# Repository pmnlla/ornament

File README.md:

# ornament
weird ahh christmas ornament shaped pcb with neopixels, stm8, and battery charging support. todo add an ftdi ig?

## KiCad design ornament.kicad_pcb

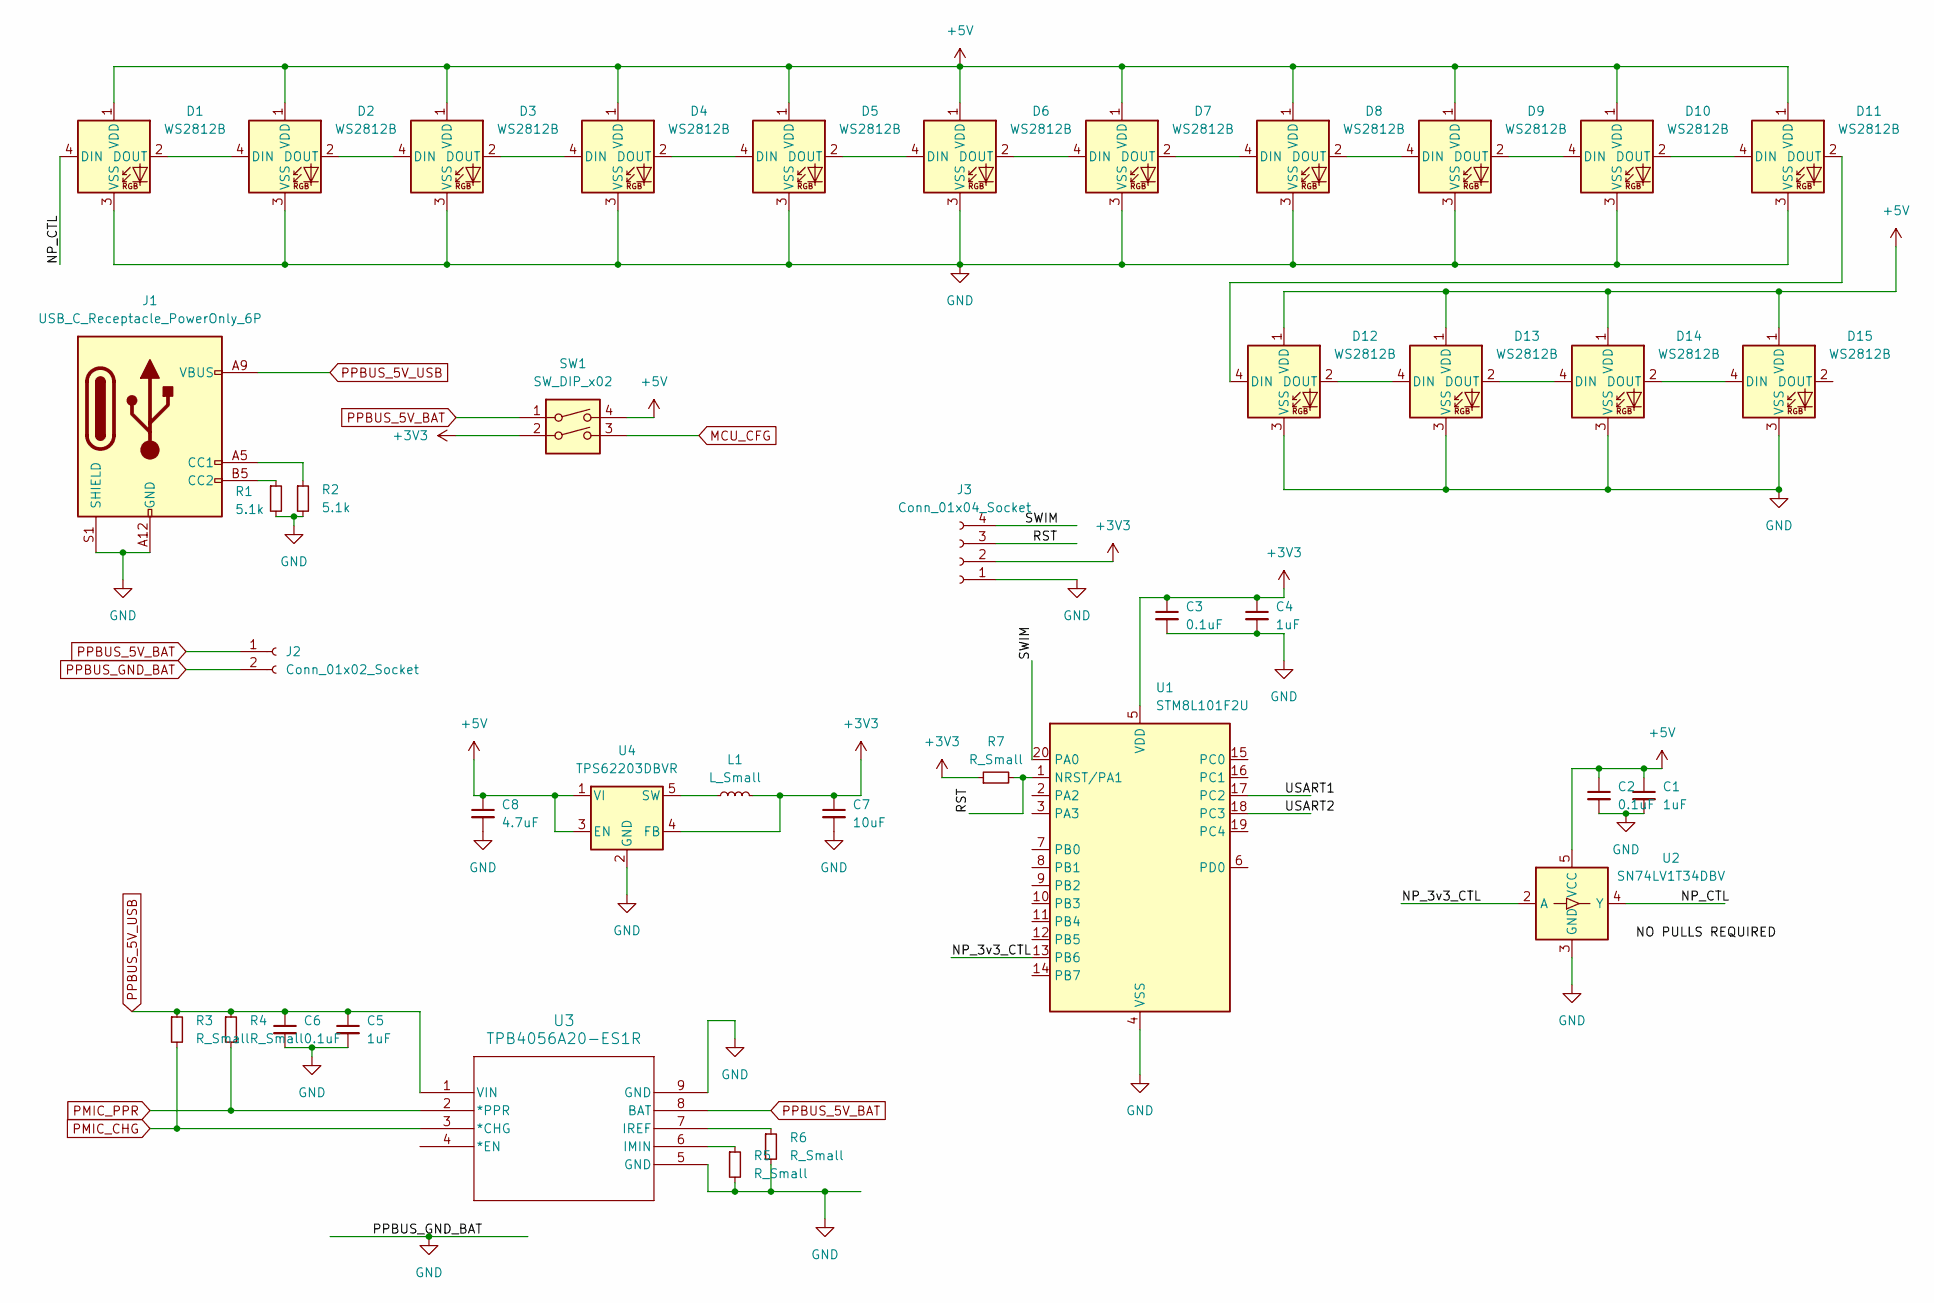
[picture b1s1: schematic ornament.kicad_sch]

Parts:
C1, C4, C5: 1uF; C_1206_3216Metric
C2, C3, C6: 0.1uF; C_1206_3216Metric
C7: 10uF; C_1206_3216Metric
C8: 4.7uF; C_1206_3216Metric
D1, D2, D3, D4, D5, D6, D7, D8, D9, D10, D11, D12, D13, D14, D15: WS2812B; LED_WS2812B_PLCC4_5.0x5.0mm_P3.2mm
J1: USB_C_Receptacle_PowerOnly_6P; USB_C_Receptacle_GCT_USB4125-xx-x-0190_6P_TopMnt_Horizontal
J2: Conn_01x02_Socket; JST_JWPF_B02B-JWPF-SK-R_1x02_P2.00mm_Vertical
J3: Conn_01x04_Socket; JST_ZE_S04B-ZESK-2D_1x04_P1.50mm_Horizontal
L1: L_Small; L_1206_3216Metric
R1, R2: 5.1k; R_1206_3216Metric
R3, R4, R5, R6, R7: R_Small; R_1206_3216Metric
SW1: SW_DIP_x02; SW_DIP_SPSTx02_Slide_6.7x6.64mm_W6.73mm_P2.54mm_LowProfile_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
U1: STM8L101F2U; ST_UFQFPN-20_3x3mm_P0.5mm
U2: SN74LV1T34DBV; SOT-23-5
U3: TPB4056A20-ES1R; ESOP-8_TPK
U4: TPS62203DBVR; SOT-23-5

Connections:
+3V3: C3.1, C4.1, C7.1, J3.2, L1.2, R7.1, SW1.2, U1.5 (VDD), U4.4 (FB)
+5V: C1.1, C2.1, C8.1, D1.1 (VDD), D2.1 (VDD), D3.1 (VDD), D4.1 (VDD), D5.1 (VDD), D6.1 (VDD), D7.1 (VDD), D8.1 (VDD), D9.1 (VDD), D10.1 (VDD), D11.1 (VDD), D12.1 (VDD), D13.1 (VDD), D14.1 (VDD), D15.1 (VDD), SW1.4, U2.5 (VCC), U4.1 (VI), U4.3 (EN)
/NP_3v3_CTL: U1.13 (PB6), U2.2 (A)
/NP_CTL: D1.4 (DIN), U2.4 (Y)
/RST: J3.3, R7.2, U1.1 (NRST/PA1)
/SWIM: J3.4, U1.20 (PA0)
/USART1: U1.17 (PC2)
/USART2: U1.18 (PC3)
MCU_CFG: SW1.3
unnamed: D1.2 (DOUT), D2.4 (DIN)
unnamed: D2.2 (DOUT), D3.4 (DIN)
unnamed: D3.2 (DOUT), D4.4 (DIN)
unnamed: D4.2 (DOUT), D5.4 (DIN)
unnamed: D5.2 (DOUT), D6.4 (DIN)
unnamed: D6.2 (DOUT), D7.4 (DIN)
unnamed: D7.2 (DOUT), D8.4 (DIN)
unnamed: D8.2 (DOUT), D9.4 (DIN)
unnamed: D9.2 (DOUT), D10.4 (DIN)
unnamed: D10.2 (DOUT), D11.4 (DIN)
unnamed: D11.2 (DOUT), D12.4 (DIN)
unnamed: D12.2 (DOUT), D13.4 (DIN)
unnamed: D13.2 (DOUT), D14.4 (DIN)
unnamed: D14.2 (DOUT), D15.4 (DIN)
unnamed: J1.A5 (CC1), R2.1
unnamed: J1.B5 (CC2), R1.1
unnamed: R5.1, U3.6 (IMIN)
unnamed: R6.1, U3.7 (IREF)
unnamed: L1.1, U4.5 (SW)
PMIC_CHG: R3.2, U3.3 (*CHG)
PMIC_PPR: R4.2, U3.2 (*PPR)
PPBUS_5V_BAT: J2.1, SW1.1, U3.8 (BAT)
PPBUS_5V_USB: C5.1, C6.1, J1.A9 (VBUS), J1.B9 (VBUS), R3.1, R4.1, U3.1 (VIN)
PPBUS_GND_BAT: C1.2, C2.2, C3.2, C4.2, C5.2, C6.2, C7.2, C8.2, D1.3 (VSS), D2.3 (VSS), D3.3 (VSS), D4.3 (VSS), D5.3 (VSS), D6.3 (VSS), D7.3 (VSS), D8.3 (VSS), D9.3 (VSS), D10.3 (VSS), D11.3 (VSS), D12.3 (VSS), D13.3 (VSS), D14.3 (VSS), D15.3 (VSS), J1.A12 (GND), J1.B12 (GND), J1.S1 (SHIELD), J2.2, J3.1, R1.2, R2.2, R5.2, R6.2, U1.4 (VSS), U2.3 (GND), U3.5 (GND), U3.9 (GND), U4.2 (GND)

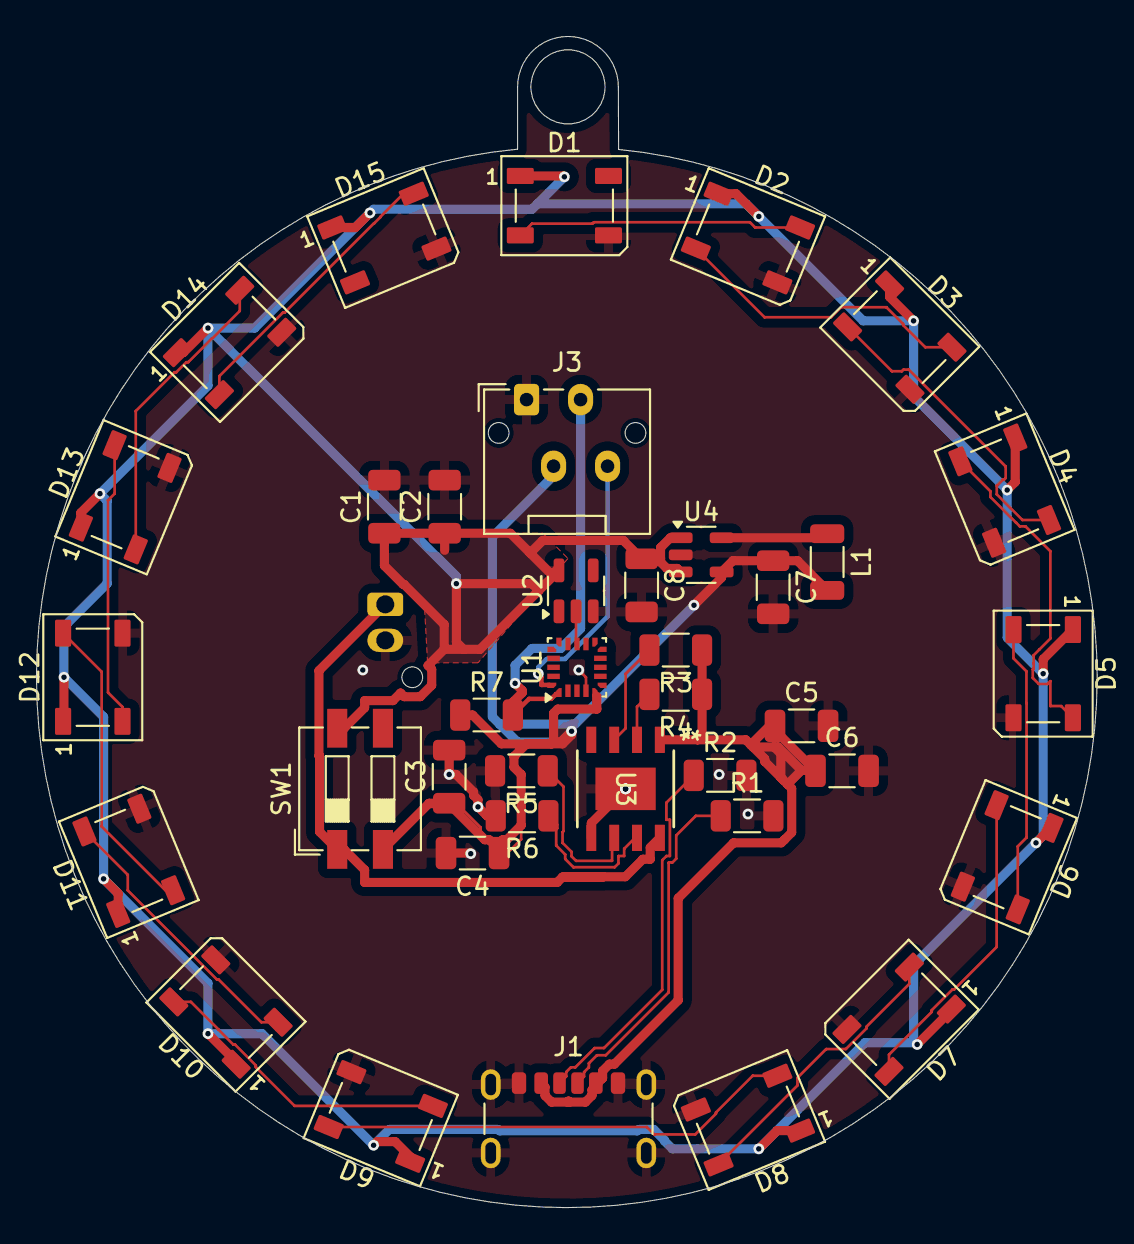
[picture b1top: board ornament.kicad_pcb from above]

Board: 2 copper layers, 58.9 x 65.1 mm, 39 parts (1 on the bottom side), 30 nets.

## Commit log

2025-01-01 upload
